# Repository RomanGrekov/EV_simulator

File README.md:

# EV_simulator
EV charge simulator

EV simulator is ntended to be test platform for DIY EVSE charge stations

EV simulator fully compatible with Level 1 and Level 2 charge stations

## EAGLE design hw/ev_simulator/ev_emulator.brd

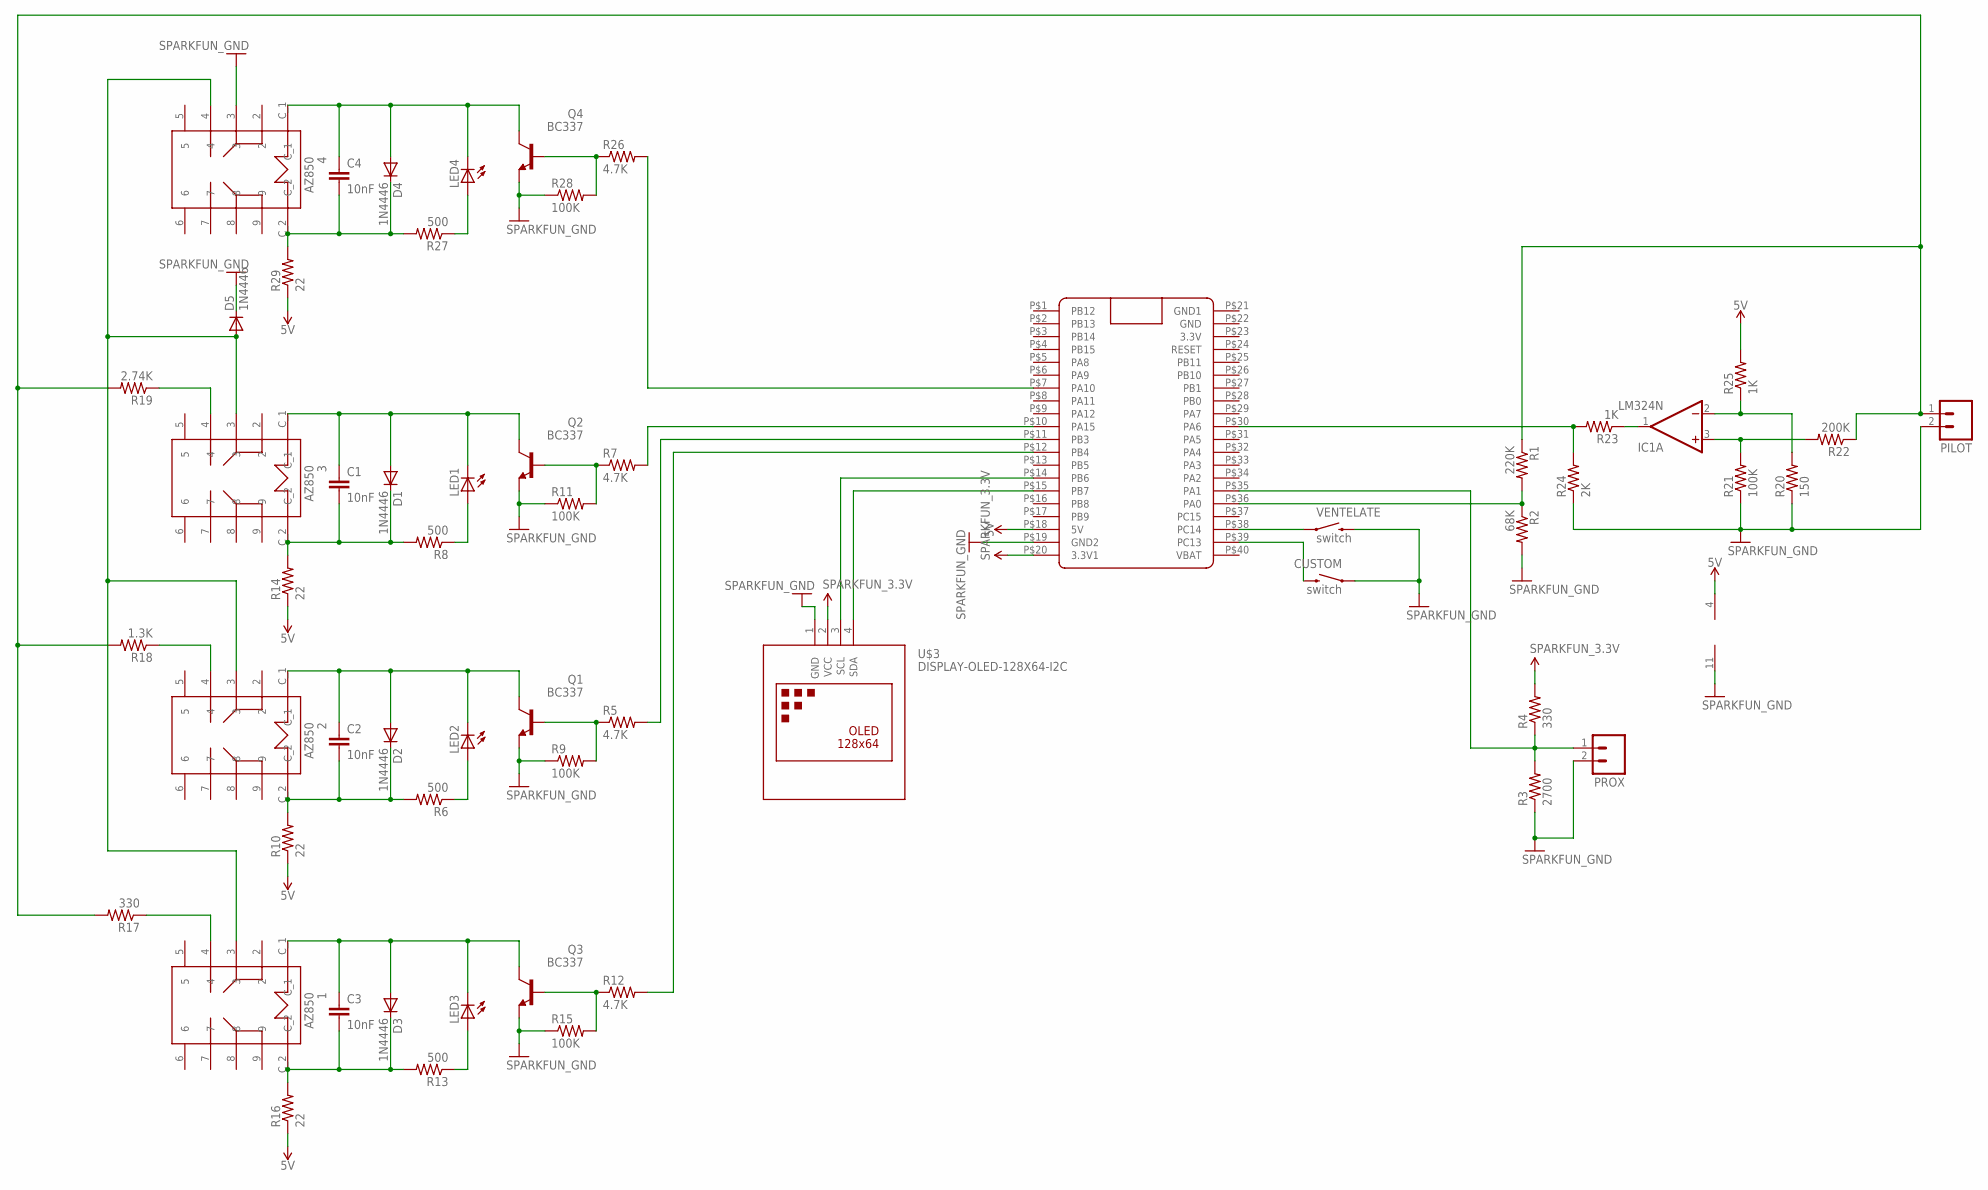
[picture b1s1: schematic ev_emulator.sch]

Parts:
1, 2, 3, 4: AZ850
C1, C2, C3, C4: 10nF; C2.5-3
CUSTOM: switch; SPARKFUN-ELECTROMECHANICAL_TACTILE-PTH
D1, D2, D3, D4, D5: 1N4446; DO35-10
IC1: LM324N; DIL14
LED1, LED2, LED3, LED4: SPARKFUN_LED-3MM-NO_SILK; SPARKFUN_LED3MM-NS
PILOT: SPARKFUN_M02POLAR; SPARKFUN_MOLEX-1X2
PROX: SPARKFUN_M02POLAR; SPARKFUN_MOLEX-1X2
Q1, Q2, Q3, Q4: BC337; TO92
R1: 220K; SPARKFUN_AXIAL-0.3
R2: 68K; SPARKFUN_AXIAL-0.3
R3: 2700; SPARKFUN_AXIAL-0.3
R4, R17: 330; SPARKFUN_AXIAL-0.3
R5, R7, R12, R26: 4.7K; SPARKFUN_AXIAL-0.3
R6, R8, R13, R27: 500; SPARKFUN_AXIAL-0.3
R9, R11, R15, R21, R28: 100K; SPARKFUN_AXIAL-0.3
R10, R14, R16, R29: 22; SPARKFUN_AXIAL-0.3
R18: 1.3K; SPARKFUN_AXIAL-0.3
R19: 2.74K; SPARKFUN_AXIAL-0.3
R20: 150; SPARKFUN_AXIAL-0.3
R22: 200K; SPARKFUN_AXIAL-0.3
R23, R25: 1K; SPARKFUN_AXIAL-0.3
R24: 2K; SPARKFUN_AXIAL-0.3
U$1: BLUE_PILL
U$3: DISPLAY-OLED-128X64-I2C
VENTELATE: switch; SPARKFUN-ELECTROMECHANICAL_TACTILE-PTH

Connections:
3.3V: R4.P$2 (2), U$1.P$20 (3.3V1), U$3.2 (VCC)
5V: IC1.4 (V+), R10.P$1 (1), R14.P$1 (1), R16.P$1 (1), R25.P$2 (2), R29.P$1 (1), U$1.P$18 (5V)
GND: 4.3, CUSTOM.1, D5.C, IC1.11 (V-), PILOT.2, PROX.2, Q1.1 (E), Q2.1 (E), Q3.1 (E), Q4.1 (E), R2.P$2 (2), R3.P$1 (1), R9.P$1 (1), R11.P$1 (1), R15.P$1 (1), R20.P$1 (1), R21.P$1 (1), R24.P$1 (1), R28.P$1 (1), U$1.P$19 (GND2), U$3.1 (GND), VENTELATE.3 (2)
GND1: U$1.P$21 (GND1)
unnamed: R26.P$2 (2), U$1.P$7 (PA10)
unnamed: R1.P$2 (2), R2.P$1 (1), U$1.P$36 (PA0)
unnamed: PROX.1, R3.P$2 (2), R4.P$1 (1), U$1.P$35 (PA1)
unnamed: Q2.2 (B), R7.P$1 (1), R11.P$2 (2)
unnamed: R12.P$2 (2), U$1.P$12 (PB4)
unnamed: 3.C_1 (С_1), C1.1, D1.A, LED1.K (C), Q2.3 (C)
unnamed: 3.C_2 (С_2), C1.2, D1.C, R8.P$2 (2), R14.P$2 (2)
unnamed: R5.P$2 (2), U$1.P$11 (PB3)
unnamed: R7.P$2 (2), U$1.P$10 (PA15)
unnamed: LED1.A, R8.P$1 (1)
unnamed: Q1.2 (B), R5.P$1 (1), R9.P$2 (2)
unnamed: 2.C_1 (С_1), C2.1, D2.A, LED2.K (C), Q1.3 (C)
unnamed: U$1.P$38 (PC14), VENTELATE.1
unnamed: U$1.P$15 (PB7), U$3.4 (SDA)
unnamed: U$1.P$14 (PB6), U$3.3 (SCL)
unnamed: 2.C_2 (С_2), C2.2, D2.C, R6.P$2 (2), R10.P$2 (2)
unnamed: CUSTOM.3 (2), U$1.P$39 (PC13)
unnamed: LED2.A, R6.P$1 (1)
unnamed: Q3.2 (B), R12.P$1 (1), R15.P$2 (2)
unnamed: 1.C_1 (С_1), C3.1, D3.A, LED3.K (C), Q3.3 (C)
unnamed: 1.C_2 (С_2), C3.2, D3.C, R13.P$2 (2), R16.P$2 (2)
unnamed: LED3.A, R13.P$1 (1)
unnamed: 1.4, R17.P$1 (1)
unnamed: R23.P$2 (2), R24.P$2 (2), U$1.P$30 (PA6)
unnamed: 2.4, R18.P$1 (1)
unnamed: 3.4, R19.P$1 (1)
unnamed: IC1.3 (+IN), R21.P$2 (2), R22.P$2 (2)
unnamed: PILOT.1, R1.P$1 (1), R17.P$2 (2), R18.P$2 (2), R19.P$2 (2), R22.P$1 (1)
unnamed: IC1.2 (-IN), R20.P$2 (2), R25.P$1 (1)
unnamed: IC1.1 (OUT), R23.P$1 (1)
unnamed: Q4.2 (B), R26.P$1 (1), R28.P$2 (2)
unnamed: 4.C_1 (С_1), C4.1, D4.A, LED4.K (C), Q4.3 (C)
unnamed: 4.C_2 (С_2), C4.2, D4.C, R27.P$2 (2), R29.P$2 (2)
unnamed: LED4.A, R27.P$1 (1)
unnamed: 1.3, 2.3, 3.3, 4.4, D5.A

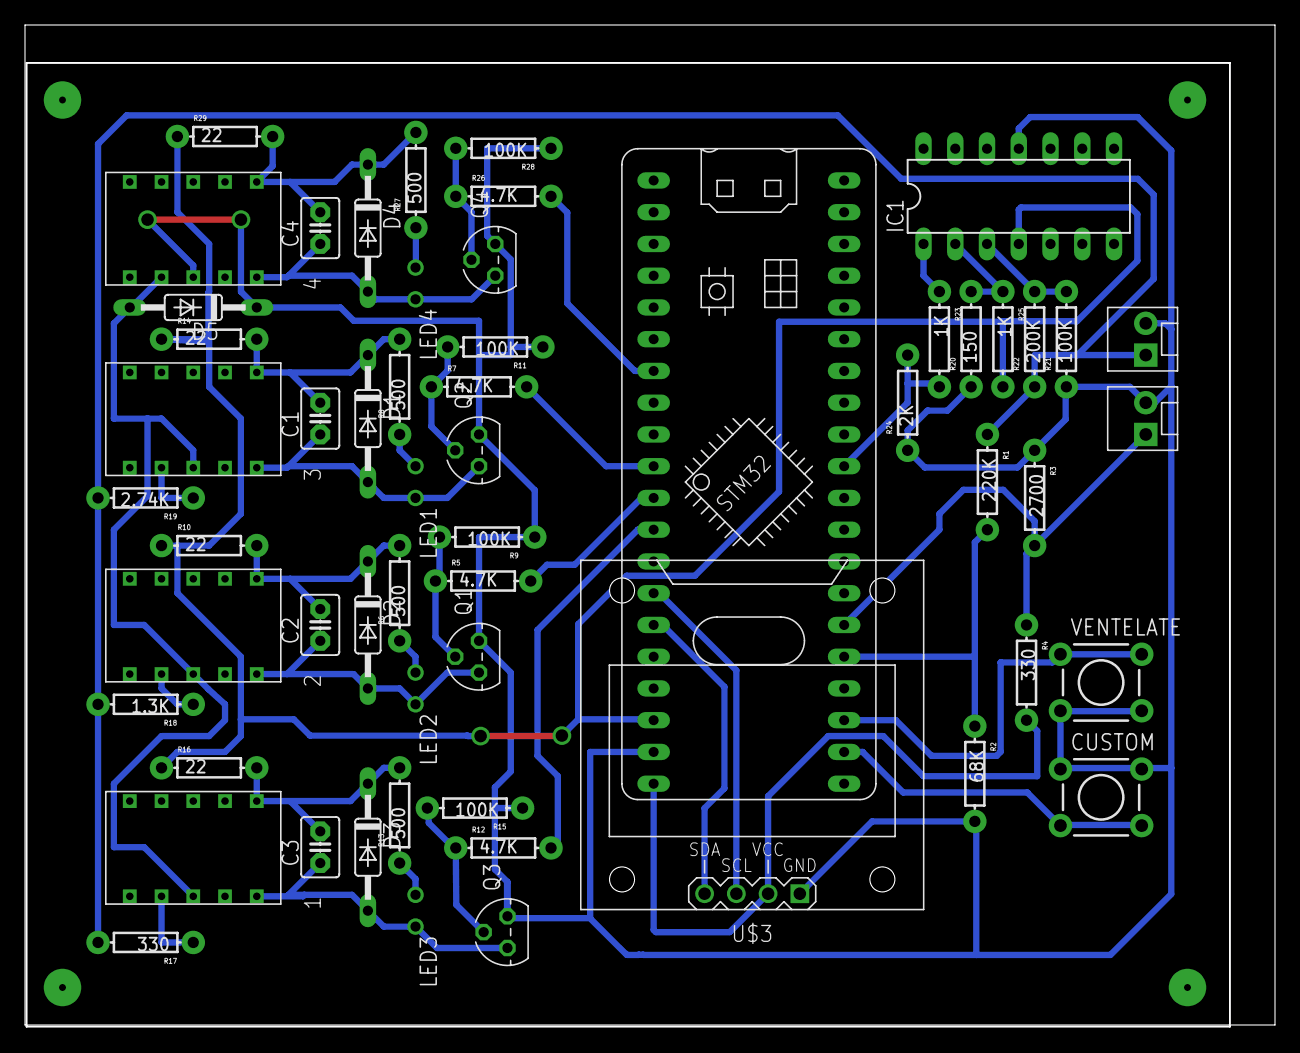
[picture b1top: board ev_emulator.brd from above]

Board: 2 copper layers, 100.0 x 80.0 mm, 57 parts (0 on the bottom side), 38 nets.

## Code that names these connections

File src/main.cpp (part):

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////////////////////////////////////////////////////////////////////////

#define OLED_ADDR 0x3c
#define BTN_1_PIN PC13
#define BTN_2_PIN PC14
#define LED_ONBOARD PC13
#define REL0 PA15
#define REL1 PB3
#define REL2 PB4
#define REL3 PA10
#define ADC_PILOT_PIN PA0
#define ADC_PROX_PIN PA1
// PA6 - Timer changel 1

// Global vars
float PilotVoltage;
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volatile bool need_adc_check = false;
volatile bool need_count_f = false;

// SDA - PB7, SCL - PB6
Adafruit_SSD1306 display(-1);

// button
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
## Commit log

2018-12-15 Added button and threads
2018-12-15 Moved btn handler to a separate thread
2018-12-16 Working on freq meter
2018-12-23 Working frequency metter
2018-12-27 Added HW design
2018-12-27 Updated scheme. Added states
2018-12-31 Updated hw and sw
2019-01-02 Added changed hw
2019-01-12 Finished working prototype

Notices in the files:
parts and their libraries:
diy-modules: Released under the Creative Commons Attribution 4.0 International License: http://creativecommons.org/licenses/by/4.0
SparkFun-PowerSymbols: Licensing: Creative Commons ShareAlike 4.0 International - https://creativecommons.org/licenses/by-sa/4.0
